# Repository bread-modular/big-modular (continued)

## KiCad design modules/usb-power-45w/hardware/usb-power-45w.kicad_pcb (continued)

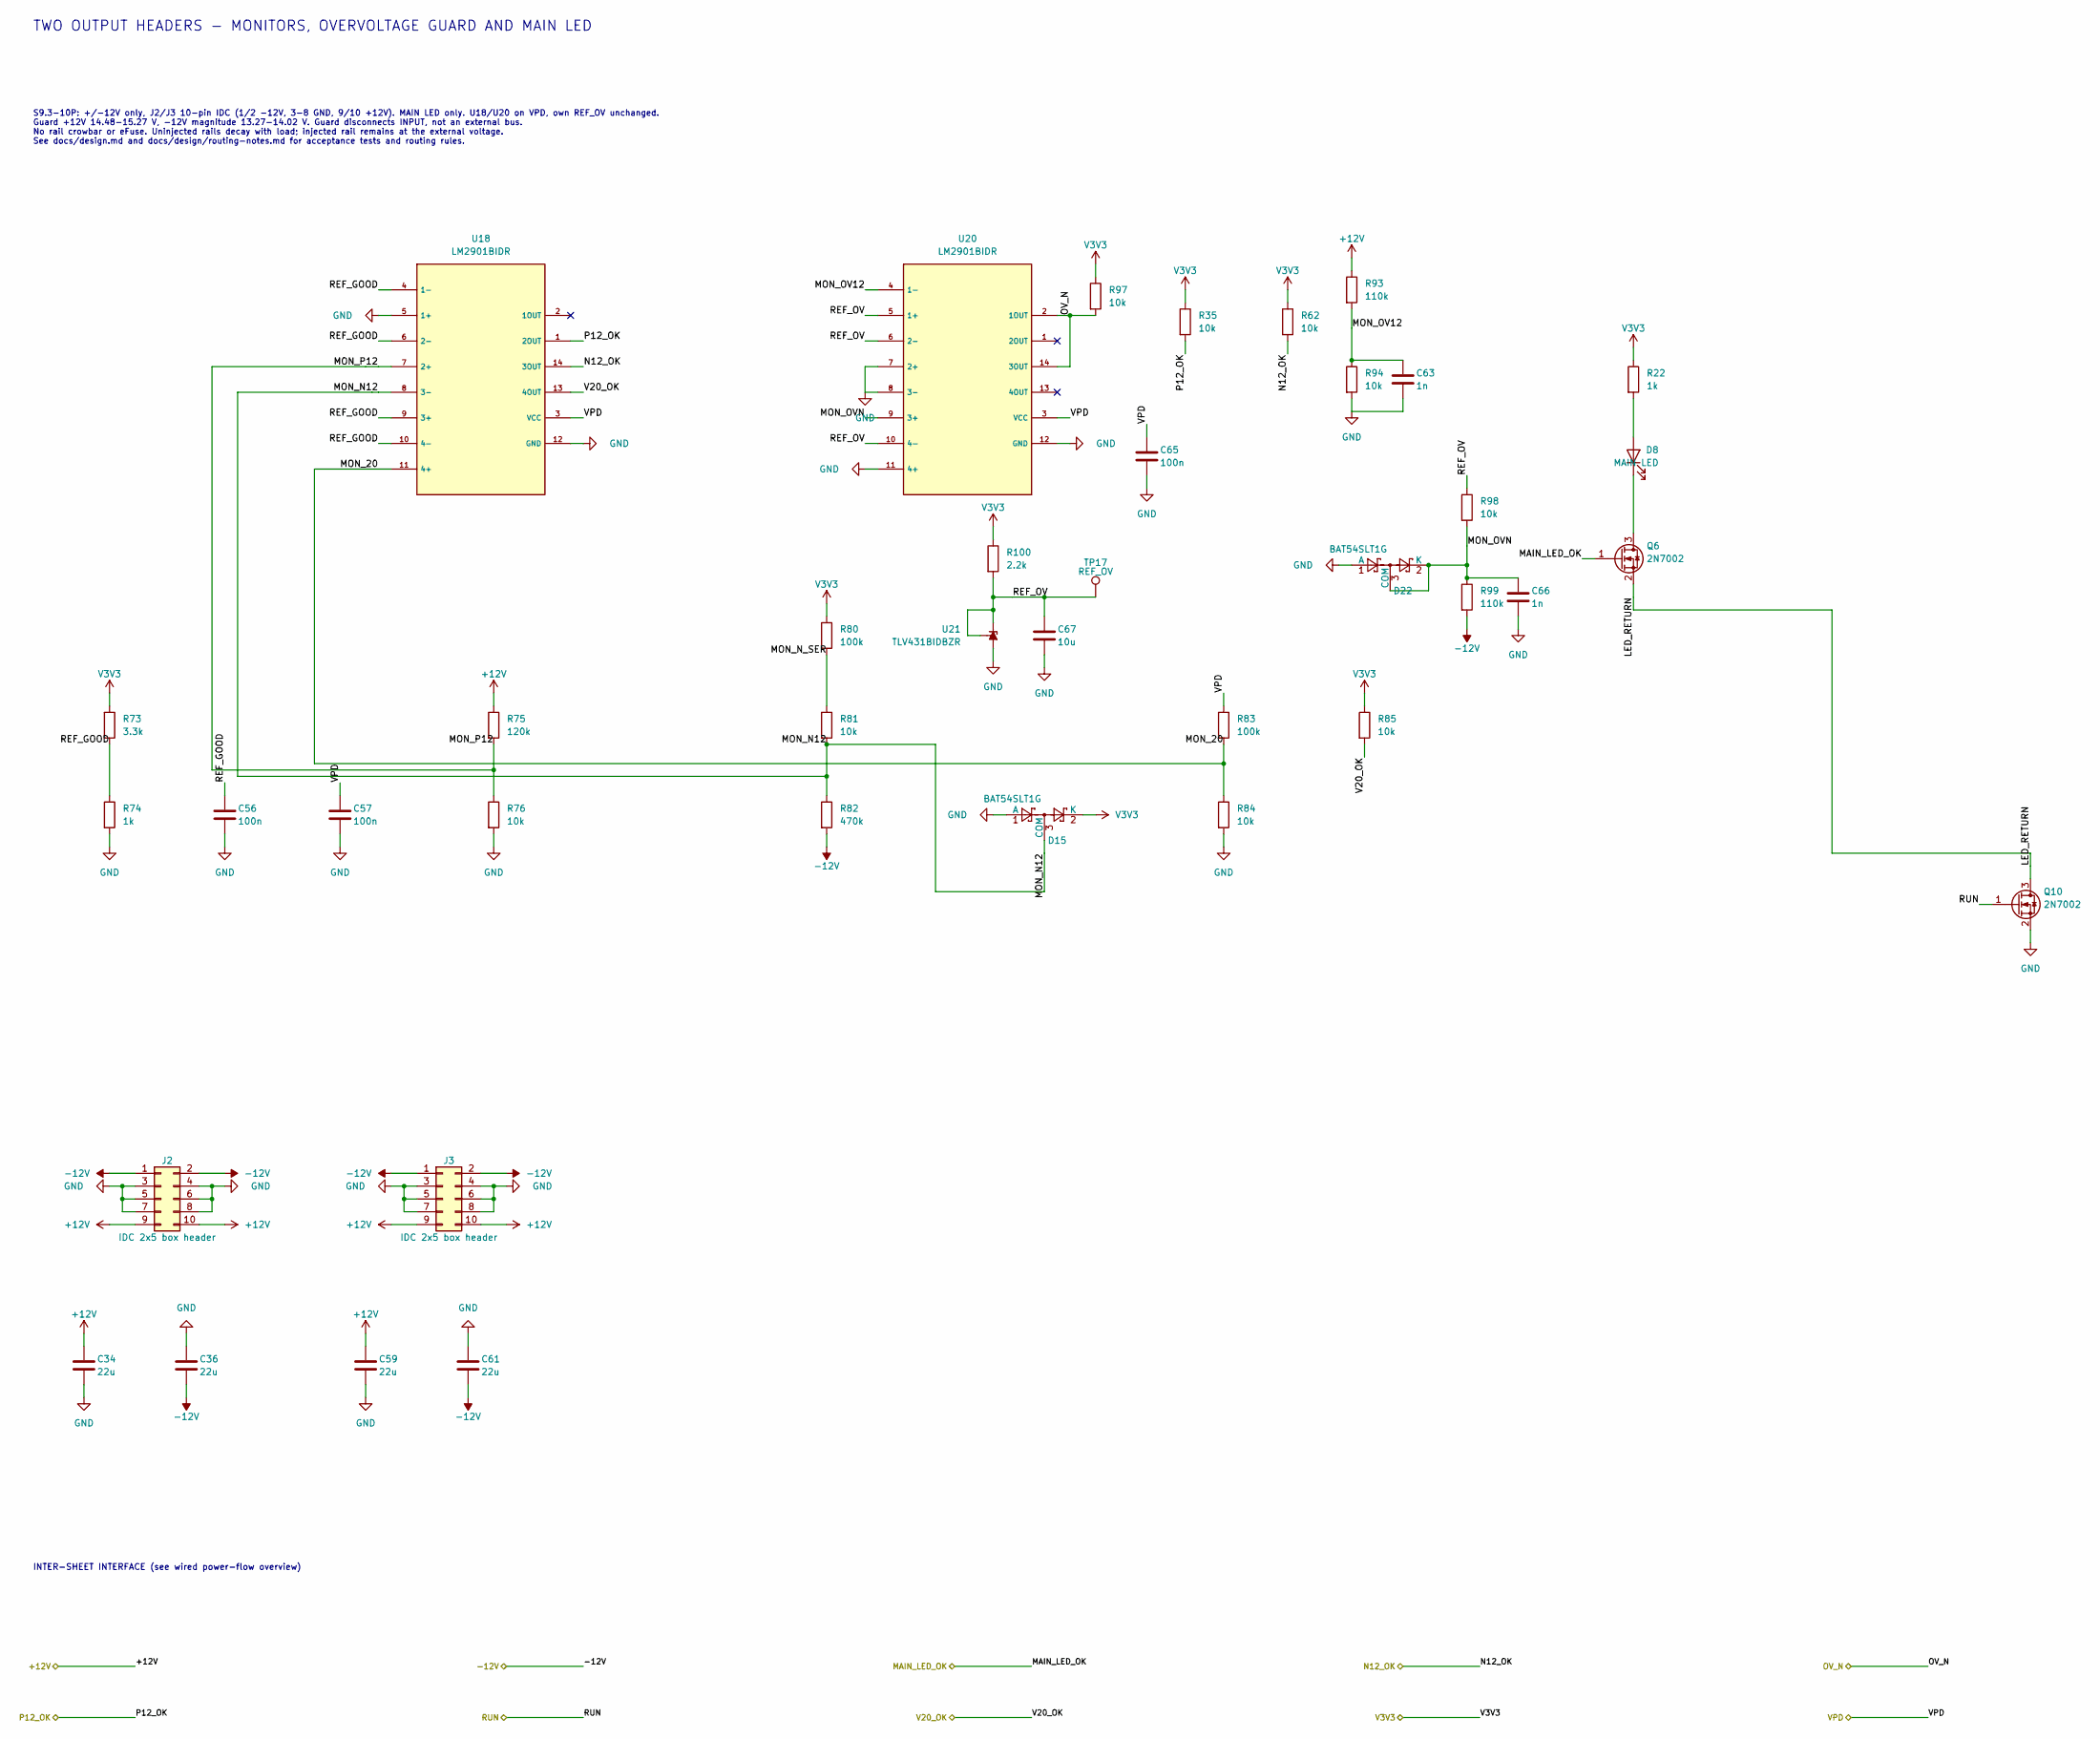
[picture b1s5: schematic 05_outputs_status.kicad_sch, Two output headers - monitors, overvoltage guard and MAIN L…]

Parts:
C34, C36, C59, C61: 22u; C_1206_3216Metric; Voltage 25V; MPN CL31A226KAHNNNE; LCSC C12891
C56, C57, C65: 100n; C_0603_1608Metric; Voltage 50V; MPN CC0603KRX7R9BB104; LCSC C14663
C63, C66: 1n; C_0603_1608Metric; Voltage 50V; MPN CL10B102KB8NNNC; LCSC C1588
C67: 10u; C_0603_1608Metric; Voltage 10V; MPN CL10A106KP8NNNC; LCSC C19702
D8: MAIN LED; LED_D3.0mm_Horizontal_O1.27mm_Z2.0mm_Edge
D15, D22: BAT54SLT1G; SOT-23; MPN BAT54SLT1G; LCSC C19726
J2, J3: IDC 2x5 box header; IDC-Header_2x05_P2.54mm_Vertical_Wurth_61201021621; MPN 61201021621
Q6, Q10: 2N7002; SOT-23; MPN 2N7002; LCSC C8545
R22, R74: 1k; R_0603_1608Metric; Tolerance 1%; MPN 0603WAF1001T5E; LCSC C21190
R35, R62, R76, R81, R84, R85, R97: 10k; R_0603_1608Metric; Tolerance 1%; MPN 0603WAF1002T5E; LCSC C25804
R73: 3.3k; R_0603_1608Metric; Tolerance 1%; MPN 0603WAF3301T5E; LCSC C22978
R75: 120k; R_0603_1608Metric; Tolerance 1%; MPN 0603WAF1203T5E; LCSC C25808
R80, R83: 100k; R_0603_1608Metric; Tolerance 1%; MPN 0603WAF1003T5E; LCSC C25803
R82: 470k; R_0603_1608Metric; Tolerance 1%; MPN 0603WAF4703T5E; LCSC C23178
R93, R99: 110k; R_0603_1608Metric; Tolerance 0.1%; MPN RT0603BRB07110KL; LCSC C860071
R94, R98: 10k; R_0603_1608Metric; Tolerance 0.1%; MPN RT0603BRD0710KL; LCSC C95204
R100: 2.2k; R_0603_1608Metric; Tolerance 1%; MPN 0603WAF2201T5E; LCSC C4190
TP17: REF_OV; TestPoint_Pad_D1.0mm
U18, U20: LM2901BIDR; SOIC-14_3.9x8.7mm_P1.27mm; MPN LM2901BIDR; LCSC C22427890
U21: TLV431BIDBZR; SOT-23; MPN TLV431BIDBZR; LCSC C398375

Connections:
+12V: C34.1, C59.1, J2.9, J2.10, J3.9, J3.10, R75.1, R93.1; also elsewhere on the board
-12V: C36.2, C61.2, J2.1, J2.2, J3.1, J3.2, R82.2, R99.2; also elsewhere on the board
/MAIN_LED_OK: Q6.1 (G); also elsewhere on the board
/N12_OK: R62.2, U18.14 (3OUT); also elsewhere on the board
/OV_N: R97.2, U20.2 (1OUT), U20.14 (3OUT); also elsewhere on the board
/P12_OK: R35.2, U18.1 (2OUT); also elsewhere on the board
/RUN: Q10.1 (G); also elsewhere on the board
/Two output headers - monitors, overvoltage guard and MAIN LED/LED_RETURN: Q6.2 (S), Q10.3 (D)
/Two output headers - monitors, overvoltage guard and MAIN LED/MON_20: R83.2, R84.1, U18.11 (4+)
/Two output headers - monitors, overvoltage guard and MAIN LED/MON_N12: D15.3 (COM), R81.2, R82.1, U18.8 (3-)
/Two output headers - monitors, overvoltage guard and MAIN LED/MON_N_SER: R80.2, R81.1
/Two output headers - monitors, overvoltage guard and MAIN LED/MON_OV12: C63.1, R93.2, R94.1, U20.4 (1-)
/Two output headers - monitors, overvoltage guard and MAIN LED/MON_OVN: C66.1, D22.2 (K), D22.3 (COM), R98.2, R99.1, U20.9 (3+)
/Two output headers - monitors, overvoltage guard and MAIN LED/MON_P12: R75.2, R76.1, U18.7 (2+)
/Two output headers - monitors, overvoltage guard and MAIN LED/REF_GOOD: C56.1, R73.2, R74.1, U18.4 (1-), U18.6 (2-), U18.9 (3+), U18.10 (4-)
/Two output headers - monitors, overvoltage guard and MAIN LED/REF_OV: C67.1, R98.1, R100.2, TP17.1 (1_1), U20.5 (1+), U20.6 (2-), U20.10 (4-), U21.1 (REF), U21.2 (K)
/V20_OK: R85.2, U18.13 (4OUT); also elsewhere on the board
/VPD: C57.1, C65.1, R83.1, U18.3 (VCC), U20.3 (VCC); also elsewhere on the board
GND: C34.2, C36.1, C56.2, C57.2, C59.2, C61.1, C63.2, C65.2, C66.2, C67.2, D15.1 (A), D22.1 (A), J2.3, J2.4, J2.5, J2.6, J2.7, J2.8, J3.3, J3.4, J3.5, J3.6, J3.7, J3.8, Q10.2 (S), R74.2, R76.2, R84.2, R94.2, U18.5 (1+), U18.12 (GND), U20.7 (2+), U20.8 (3-), U20.11 (4+), U20.12 (GND), U21.3 (A); also elsewhere on the board
unnamed: D8.2 (A), R22.2
unnamed: D8.1 (K), Q6.3 (D)
V3V3: D15.2 (K), R22.1, R35.1, R62.1, R73.1, R80.1, R85.1, R97.1, R100.1; also elsewhere on the board

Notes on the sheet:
TWO OUTPUT HEADERS - MONITORS, OVERVOLTAGE GUARD AND MAIN LED
INTER-SHEET INTERFACE (see wired power-flow overview)
S9.3-10P: +/-12V only, J2/J3 10-pin IDC (1/2 -12V, 3-8 GND, 9/10 +12V). MAIN LED only. U18/U20 on VPD, own REF_OV unchanged. Guard +12V 14.48-15.27 V, -12V magnitude 13.27-14.02 V. Guard disconnects INPUT, not an external bus. No rail crowbar or eFuse. Uninjected rails decay with load; injected rai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

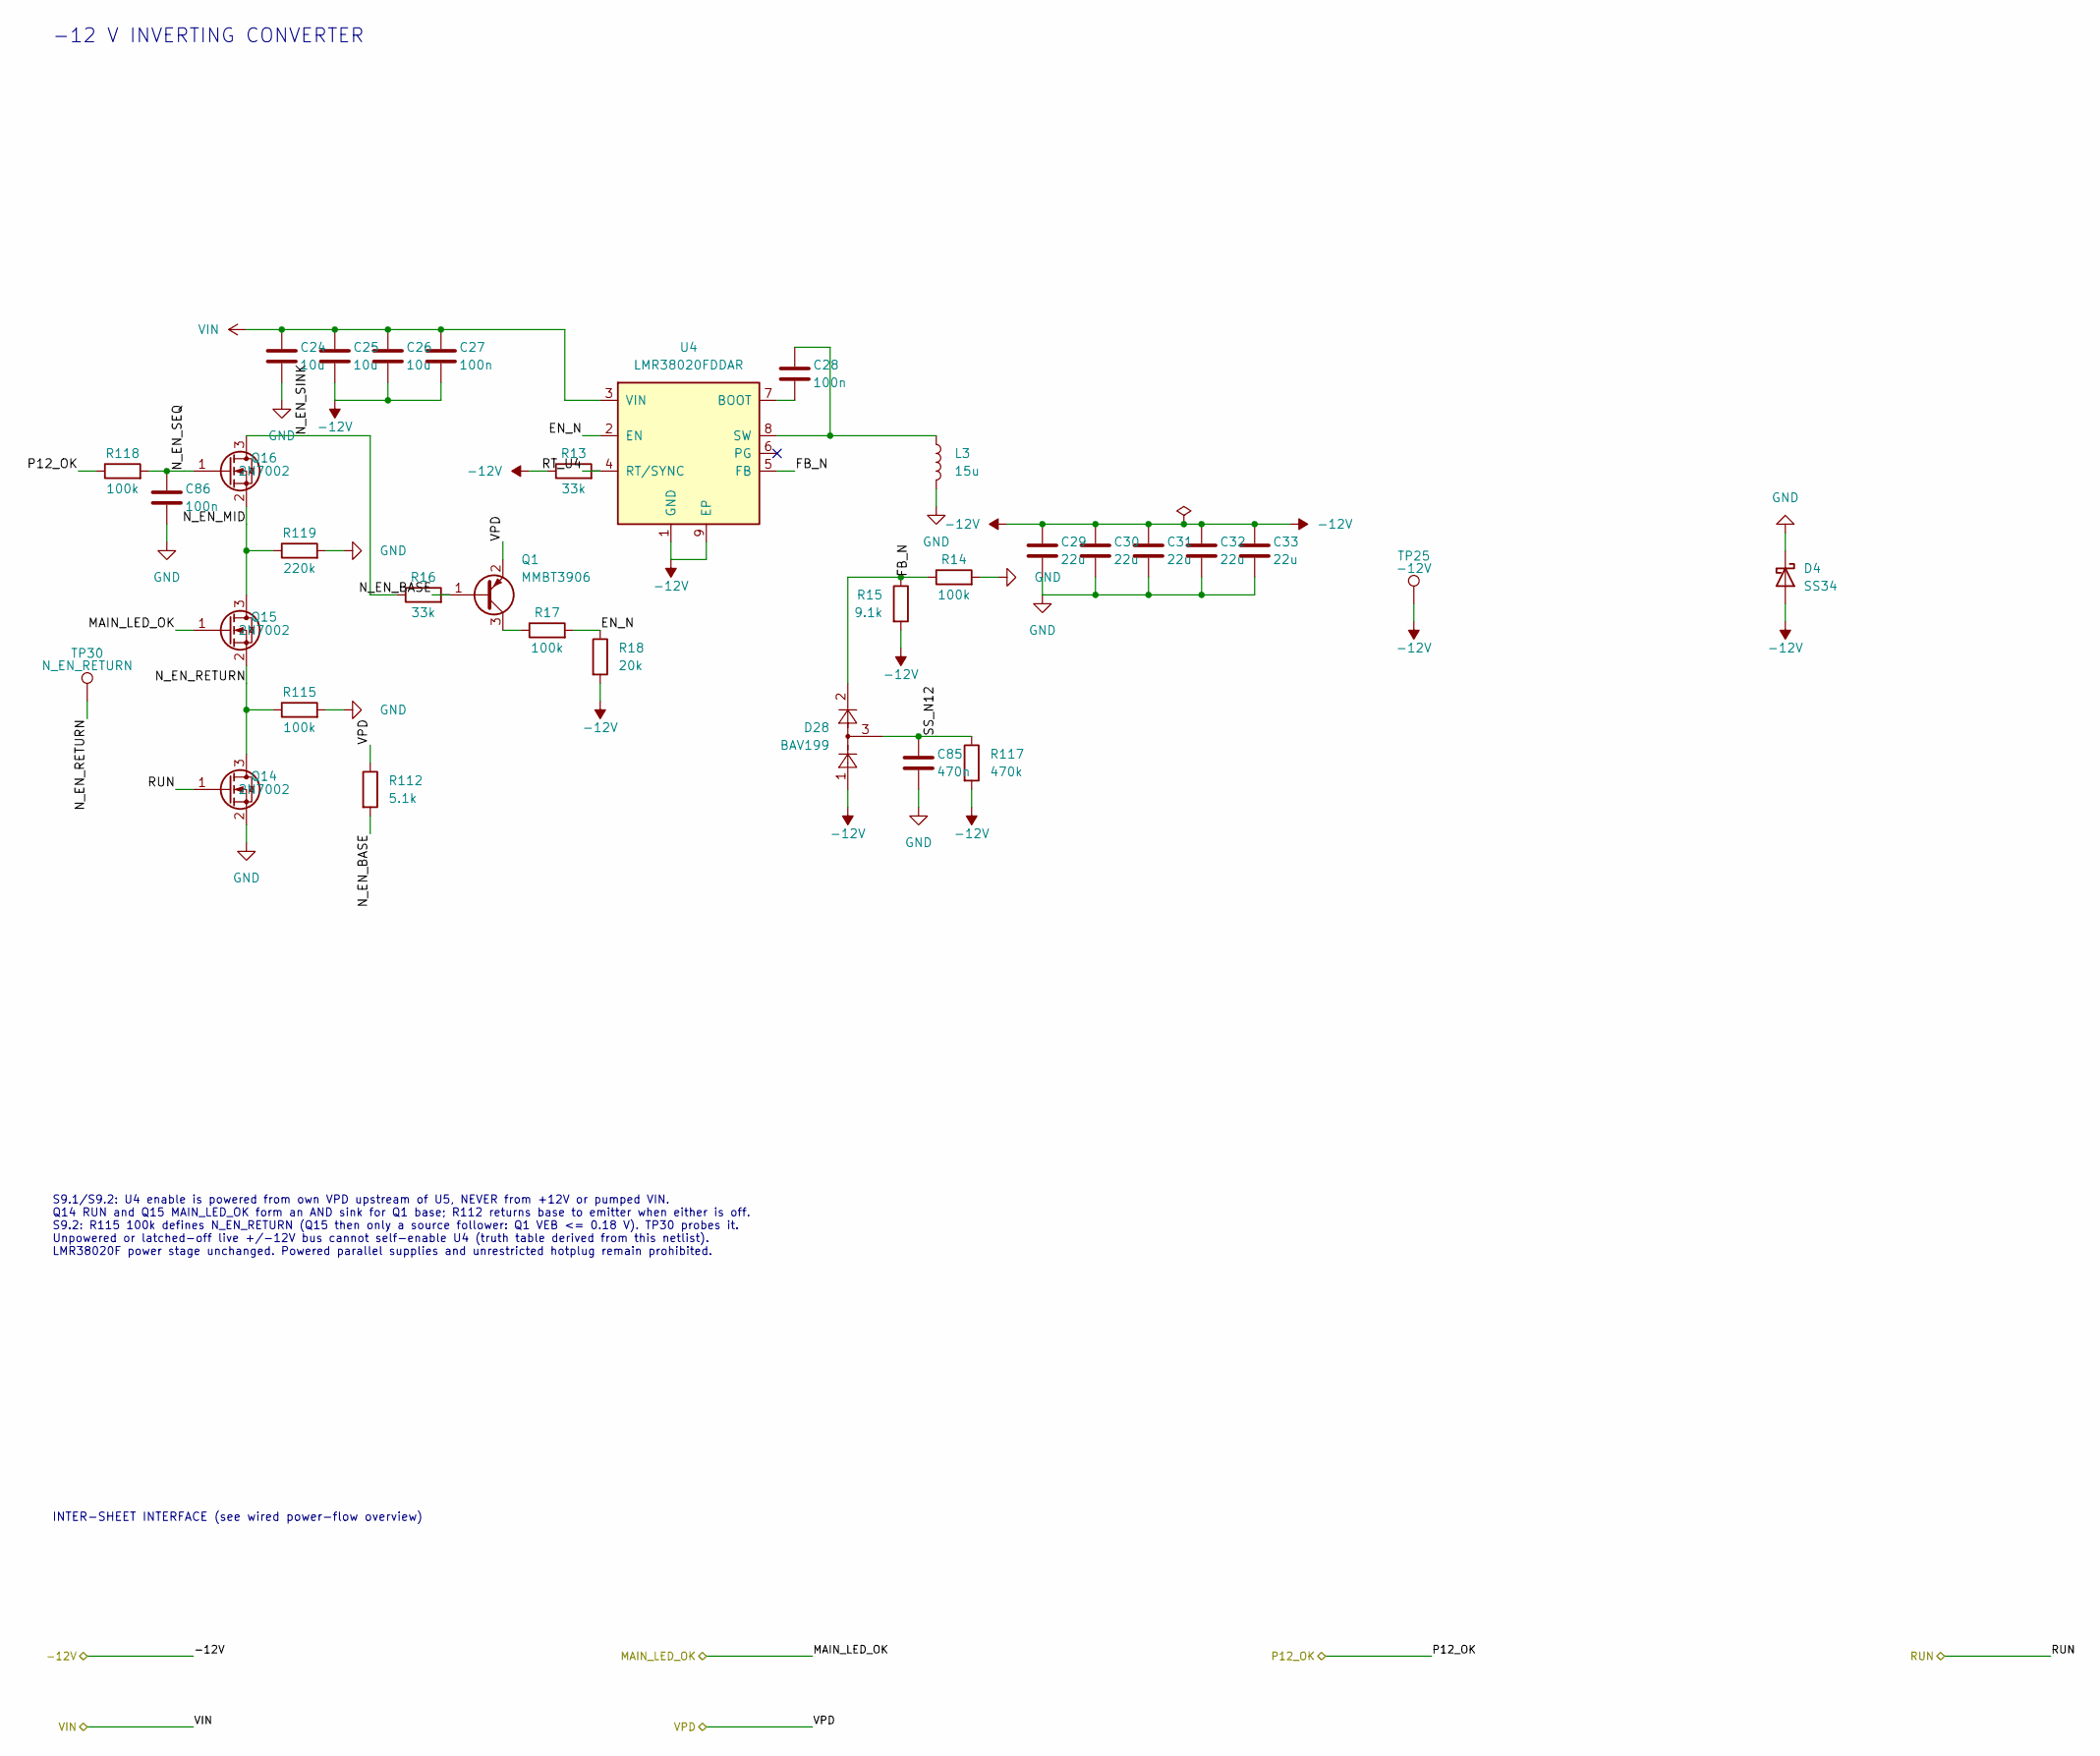
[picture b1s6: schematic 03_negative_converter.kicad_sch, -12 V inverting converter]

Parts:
C24, C25, C26: 10u; C_1206_3216Metric; Voltage 50V; MPN CL31A106KBHNNNE; LCSC C13585
C27, C28, C86: 100n; C_0603_1608Metric; Voltage 50V; MPN CC0603KRX7R9BB104; LCSC C14663
C29, C30, C31, C32, C33: 22u; C_1206_3216Metric; Voltage 25V; MPN CL31A226KAHNNNE; LCSC C12891
C85: 470n; C_0603_1608Metric; Voltage 25V; MPN CL10B474KA8NNNC; LCSC C1623
D4: SS34; D_SMA; MPN SS34; LCSC C8678
D28: BAV199; SOT-23; MPN BAV199LT1G; LCSC C145516
L3: 15u; L_SLO1040H6R8MTT; MPN SLO1040H150MTT; LCSC C182184
Q1: MMBT3906; SOT-23; MPN MMBT3906LT1G; LCSC C53444
Q14, Q15, Q16: 2N7002; SOT-23; MPN 2N7002; LCSC C8545
R13, R16: 33k; R_0603_1608Metric; Tolerance 1%; MPN 0603WAF3302T5E; LCSC C4216
R14, R17, R115, R118: 100k; R_0603_1608Metric; Tolerance 1%; MPN 0603WAF1003T5E; LCSC C25803
R15: 9.1k; R_0603_1608Metric; Tolerance 1%; MPN 0603WAF9101T5E; LCSC C23260
R18: 20k; R_0603_1608Metric; Tolerance 1%; MPN 0603WAF2002T5E; LCSC C4184
R112: 5.1k; R_0603_1608Metric; Tolerance 1%; MPN 0603WAF5101T5E; LCSC C23186
R117: 470k; R_0603_1608Metric; Tolerance 1%; MPN 0603WAF4703T5E; LCSC C23178
R119: 220k; R_0603_1608Metric; Tolerance 1%; MPN 0603WAF2203T5E; LCSC C22961
TP25: -12V; TestPoint_Pad_D1.5mm
TP30: N_EN_RETURN; TestPoint_Pad_D1.5mm
U4: LMR38020FDDAR; TI_SO-PowerPAD-8_NoViaInPad; MPN LMR38020FDDAR; LCSC C5149193

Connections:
-12V: C25.2, C26.2, C27.2, C29.1, C30.1, C31.1, C32.1, C33.1, D4.2 (A), D28.1 (A), R13.1, R15.2, R18.2, R117.2, TP25.1 (1_1), U4.1 (GND), U4.9 (EP); also elsewhere on the board
/-12 V inverting converter/EN_N: R17.2, R18.1, U4.2 (EN)
/-12 V inverting converter/FB_N: D28.2 (K), R14.1, R15.1, U4.5 (FB)
/-12 V inverting converter/N_EN_BASE: Q1.1 (B), R16.2, R112.2
/-12 V inverting converter/N_EN_MID: Q15.3 (D), Q16.2 (S), R119.1
/-12 V inverting converter/N_EN_RETURN: Q14.3 (D), Q15.2 (S), R115.1, TP30.1 (1_1)
/-12 V inverting converter/N_EN_SEQ: C86.1, Q16.1 (G), R118.2
/-12 V inverting converter/N_EN_SINK: Q16.3 (D), R16.1
/-12 V inverting converter/RT_U4: R13.2, U4.4 (RT/SYNC)
/-12 V inverting converter/SS_N12: C85.1, D28.3 (COM), R117.1
/MAIN_LED_OK: Q15.1 (G); also elsewhere on the board
/P12_OK: R118.1; also elsewhere on the board
/RUN: Q14.1 (G); also elsewhere on the board
/VPD: Q1.2 (E), R112.1; also elsewhere on the board
GND: C24.2, C29.2, C30.2, C31.2, C32.2, C33.2, C85.2, C86.2, D4.1 (K), L3.2, Q14.2 (S), R14.2, R115.2, R119.2; also elsewhere on the board
unnamed: Q1.3 (C), R17.1
unnamed: C28.2, U4.7 (BOOT)
unnamed: C28.1, L3.1, U4.8 (SW)
VIN: C24.1, C25.1, C26.1, C27.1, U4.3 (VIN); also elsewhere on the board

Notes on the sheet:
-12 V INVERTING CONVERTER
INTER-SHEET INTERFACE (see wired power-flow overview)
S9.1/S9.2: U4 enable is powered from own VPD upstream of U5, NEVER from +12V or pumped VIN. Q14 RUN and Q15 MAIN_LED_OK form an AND sink for Q1 base; R112 returns base to emitter when either is off. S9.2: R115 100k defines N_EN_RETURN (Q15 then only a source follower: Q1 VEB <= 0.18 V). TP30 probes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

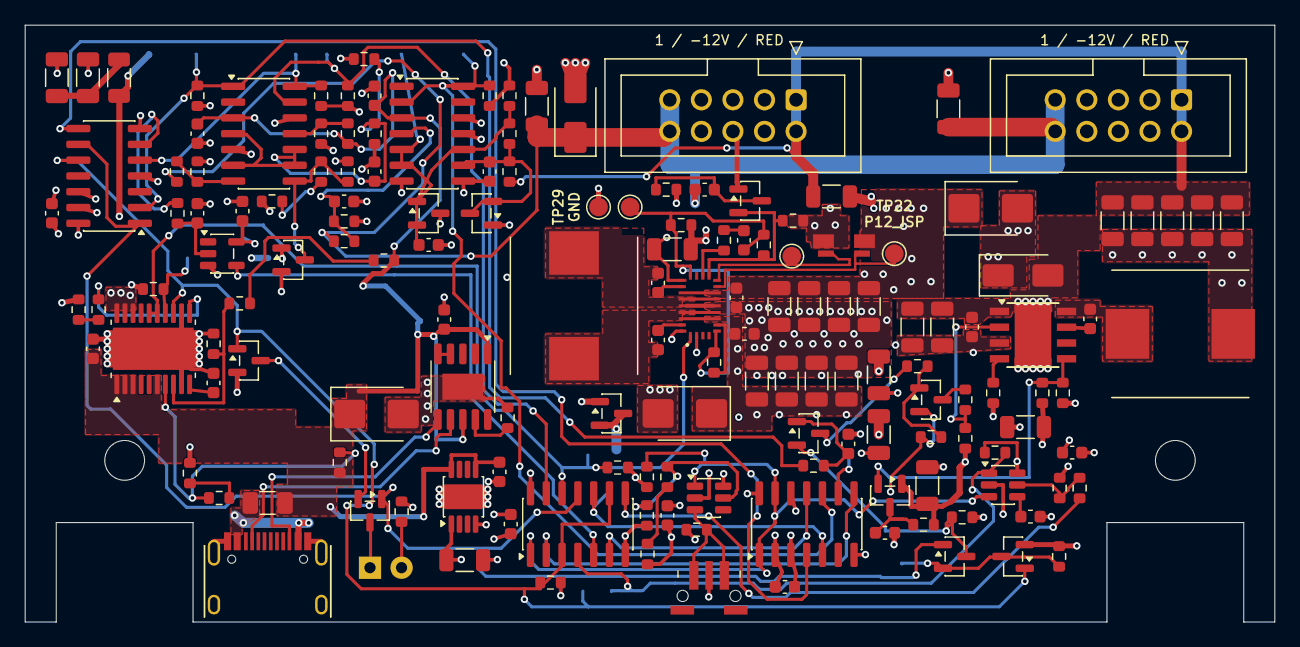
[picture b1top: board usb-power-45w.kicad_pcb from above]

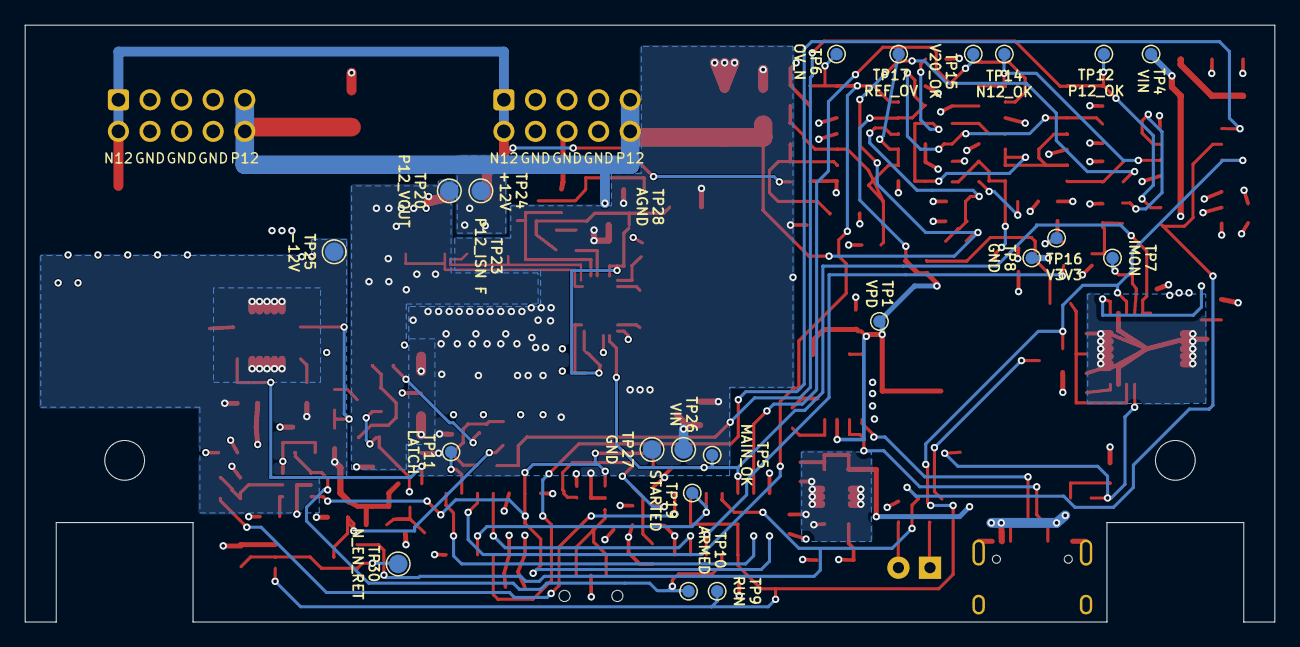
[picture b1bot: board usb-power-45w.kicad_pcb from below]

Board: 4 copper layers, 100.5 x 48.0 mm, 176 parts (21 on the bottom side), 80 nets.
